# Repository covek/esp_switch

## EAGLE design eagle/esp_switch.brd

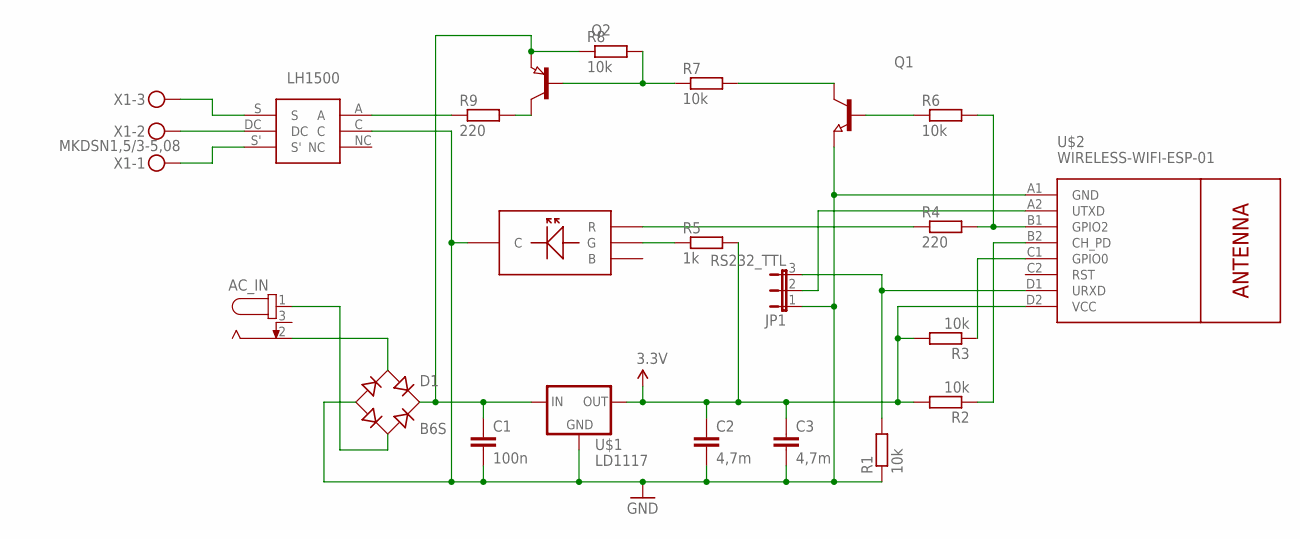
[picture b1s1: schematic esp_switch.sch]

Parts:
AC_IN: 694108301002
C1: 100n; C0805
C2, C3: 4,7m; C0805
D1: B6S; MBS
JP1: RS232_TTL; JP2
LH1500: LH1500
Q1: NPN-TRANSISTOR_SOT23; SOT23
Q2: PNP-TRANSISTOR_SOT23; SOT23
R1, R2, R3, R6, R7, R8: 10k; R0805
R4, R9: 220; R0805
R5: 1k; R0805
RGBLED5MM: RGB_LEDA; RGB_LED
U$1: LD1117
U$2: WIRELESS-WIFI-ESP-01
X1: MKDSN1,5/3-5,08

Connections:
3.3V: C2.1, C3.1, R2.2, R3.2, R5.2, U$1.OUT, U$2.D2 (VCC)
GND: C1.2, C2.2, C3.2, D1.-, JP1.1, LH1500.C, Q1.2 (E), R1.1, RGBLED5MM.P$3 (C), U$1.GND, U$2.A1 (GND)
unnamed: AC_IN.2, D1.AC1
unnamed: LH1500.S, X1.3
unnamed: AC_IN.1, D1.AC2
unnamed: JP1.3, R1.2, U$2.D1 (URXD)
unnamed: JP1.2, U$2.A2 (UTXD)
unnamed: C1.1, D1.+, Q2.2 (E), R8.1, U$1.IN
unnamed: LH1500.DC, X1.2
unnamed: R3.1, U$2.C1 (GPIO0)
unnamed: R2.1, U$2.B2 (CH_PD)
unnamed: R4.2, R6.2, U$2.B1 (GPIO2)
unnamed: R5.1, RGBLED5MM.P$2 (G)
unnamed: R4.1, RGBLED5MM.P$4 (R)
unnamed: Q2.3 (C), R9.2
unnamed: LH1500.S', X1.1
unnamed: Q2.1 (B), R7.1, R8.2
unnamed: Q1.3 (C), R7.2
unnamed: Q1.1 (B), R6.1
unnamed: LH1500.A, R9.1

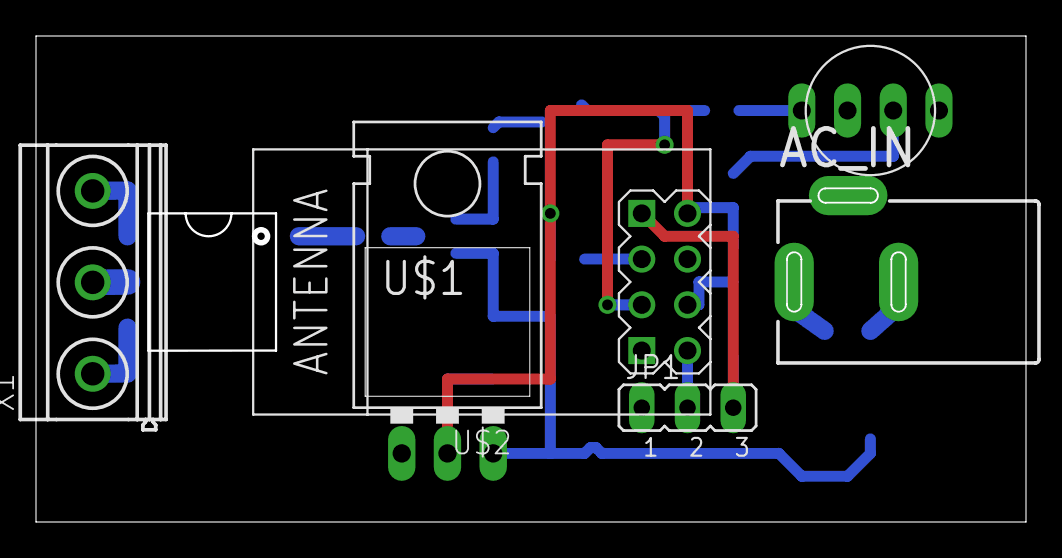
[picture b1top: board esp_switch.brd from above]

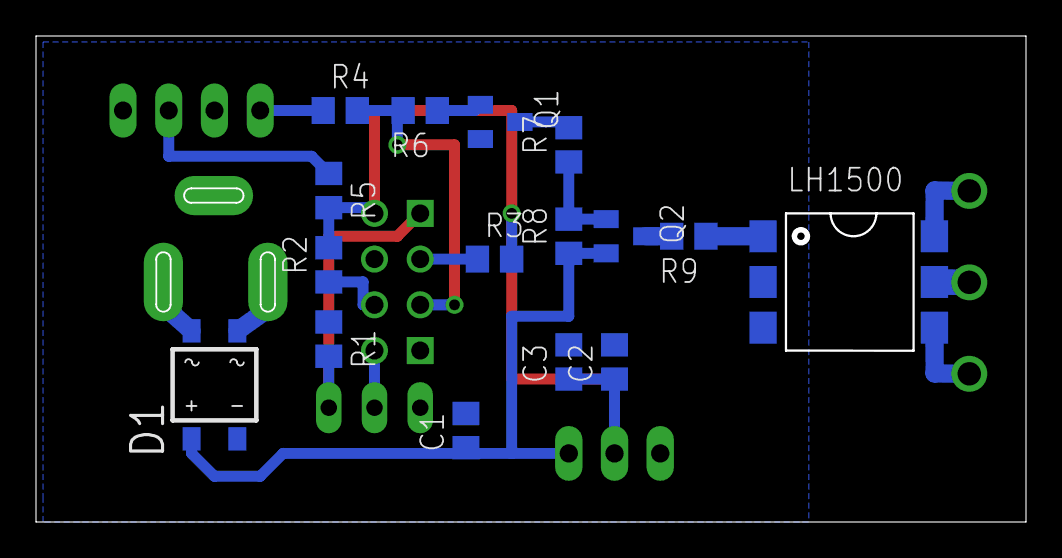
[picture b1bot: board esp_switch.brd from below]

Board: 2 copper layers, 54.7 x 26.7 mm, 22 parts (16 on the bottom side), 20 nets.

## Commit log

2017-03-07 add eagle files
2017-03-07 add RGB LED
2017-03-07 Add transistors and etc.
2017-03-08 modified brd size for case and add out port,SSR to sch, brd
2017-03-08 brd modified2
2017-03-08 update sch and brd
2017-03-09 add code for ESP
2017-03-09 changed AC power connector, optimized milling

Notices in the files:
parts and their libraries:
diy-modules: Released under the Creative Commons Attribution 4.0 International License: http://creativecommons.org/licenses/by/4.0
Wurth_Elektronik_Electromechanic_DC_Powe: Copyright: Würth Elektronik
